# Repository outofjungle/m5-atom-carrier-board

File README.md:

# M5Atom WiFi Config Board

## Schematic

## Front

## Back

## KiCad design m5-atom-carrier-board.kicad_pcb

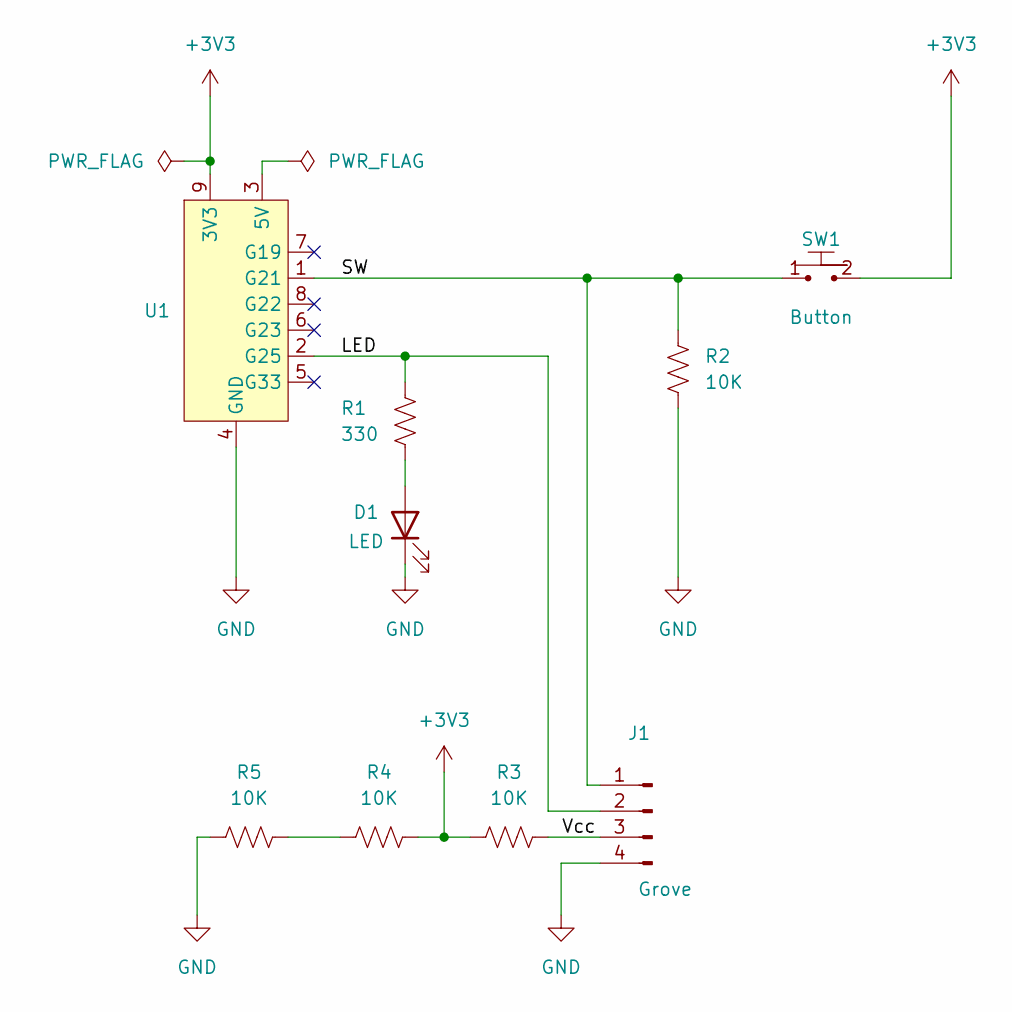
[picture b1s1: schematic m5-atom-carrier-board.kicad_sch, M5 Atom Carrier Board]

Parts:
D1: LED; LED_0805_2012Metric_Pad1.15x1.40mm_HandSolder
J1: Grove; NS-Tech_Grove_1x04_P2mm_Vertical
R1: 330; R_0805_2012Metric_Pad1.20x1.40mm_HandSolder
R2, R3, R4, R5: 10K; R_0805_2012Metric_Pad1.20x1.40mm_HandSolder
SW1: Button; SparkFun_COM-08720
U1: M5Atom

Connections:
+3V3: R3.1, R4.2, SW1.2, U1.9 (3V3)
/LED: J1.2, R1.1, U1.2 (G25)
/SW: J1.1, R2.1, SW1.1, U1.1 (G21)
/Vcc: J1.3, R3.2
GND: D1.1 (K), J1.4, R2.2, R5.1, U1.4 (GND)
unnamed: D1.2 (A), R1.2
unnamed: R4.1, R5.2

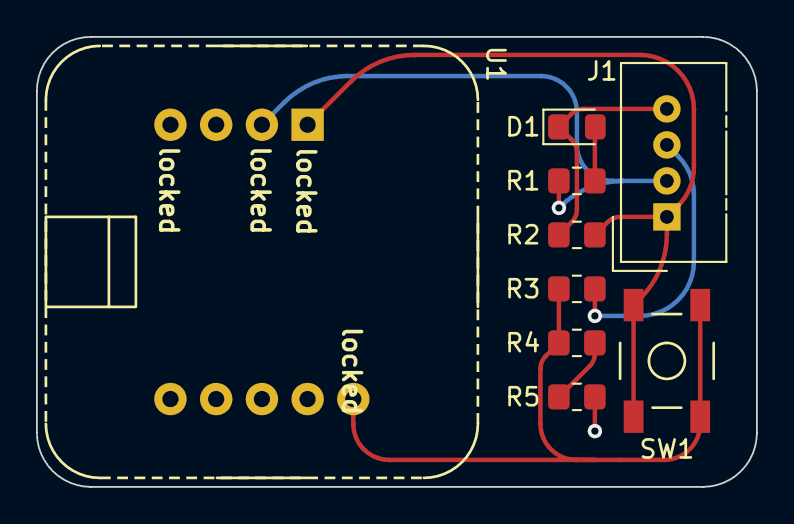
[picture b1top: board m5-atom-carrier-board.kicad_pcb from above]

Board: 2 copper layers, 40.0 x 25.0 mm, 9 parts (0 on the bottom side), 7 nets.

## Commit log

2023-11-14 board version v0.1
2023-11-15 minor adjustments
2023-11-15 generate gerber files
2023-11-15 re-generate gerber files
